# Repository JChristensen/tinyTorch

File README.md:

# tinyTorch #
https://github.com/JChristensen/tinyTorch  
https://github.com/JChristensen/tinyTorch-fw  
README file  
Jack Christensen Jan-2017

## Introduction ##

**tinyTorch** is a small LED flashlight controlled by an [ATtiny84A](http://www.atmel.com/devices/ATTINY84A.aspx) microcontroller. Choose white light for best illumination, or red light to preserve night vision. Eight brightness levels are selectable. The circuit can be programmed to power off automatically; two power-off intervals are available.

**tinyTorch** runs on two AA cells. Any type will work, including alkaline, standard carbon/zinc or rechargeable types (NiMH, NiCd). A boost regulator keeps the supply voltage and therefore the LED brightness constant as the batteries age. Because of the boost circuit, **tinyTorch** can run on batteries that will no longer power other devices, more nearly extracting all the energy available from the batteries. The microcontroller monitors the voltage and automatically shuts the circuit off when the batteries are exhausted to prevent leakage.

[Hardware design](https://github.com/JChristensen/tinyTorch) and [firmware](https://github.com/JChristensen/tinyTorch-fw) are available on GitHub.  
PC boards can be ordered from [OSH Park](https://www.oshpark.com/shared_projects/fUhQEilO).  
A bill of materials is available at [Mouser Electronics](https://www.mouser.com/ProjectManager/ProjectDetail.aspx?AccessID=e556f7b439) and also in the [hardware repo](https://github.com/JChristensen/tinyTorch).

## Operation ##

Press either button to turn **tinyTorch** on. The last color and brightness are remembered.
Press UP/COLOR to increase brightness; press DOWN/OFF to decrease.
Press and hold UP/COLOR to change between the white and red LEDs.
Press and hold DOWN/OFF to turn off.

To program **tinyTorch** to turn off automatically after one minute:
- Remove one battery.
- Press and hold the DOWN/OFF button.
- Insert the battery.
- Release DOWN/OFF.

To program **tinyTorch** to turn off automatically after five minutes, use the steps above but press and hold the UP/COLOR button instead.

To disable the automatic turn-off feature, use the steps above but press and hold both buttons instead.

When the batteries are exhausted, **tinyTorch** will blink the red and white LEDs alternately and then turn off. The brightness levels will be set to the minimum values. This may allow **tinyTorch** to continue to operate at a lower brightness level for a limited time but it is advisable to replace the batteries soon to prevent leakage.

## CC BY-SA ##
"tinyTorch" by Jack Christensen is licensed under [CC BY-SA 4.0](https://creativecommons.org/licenses/by-sa/4.0/).

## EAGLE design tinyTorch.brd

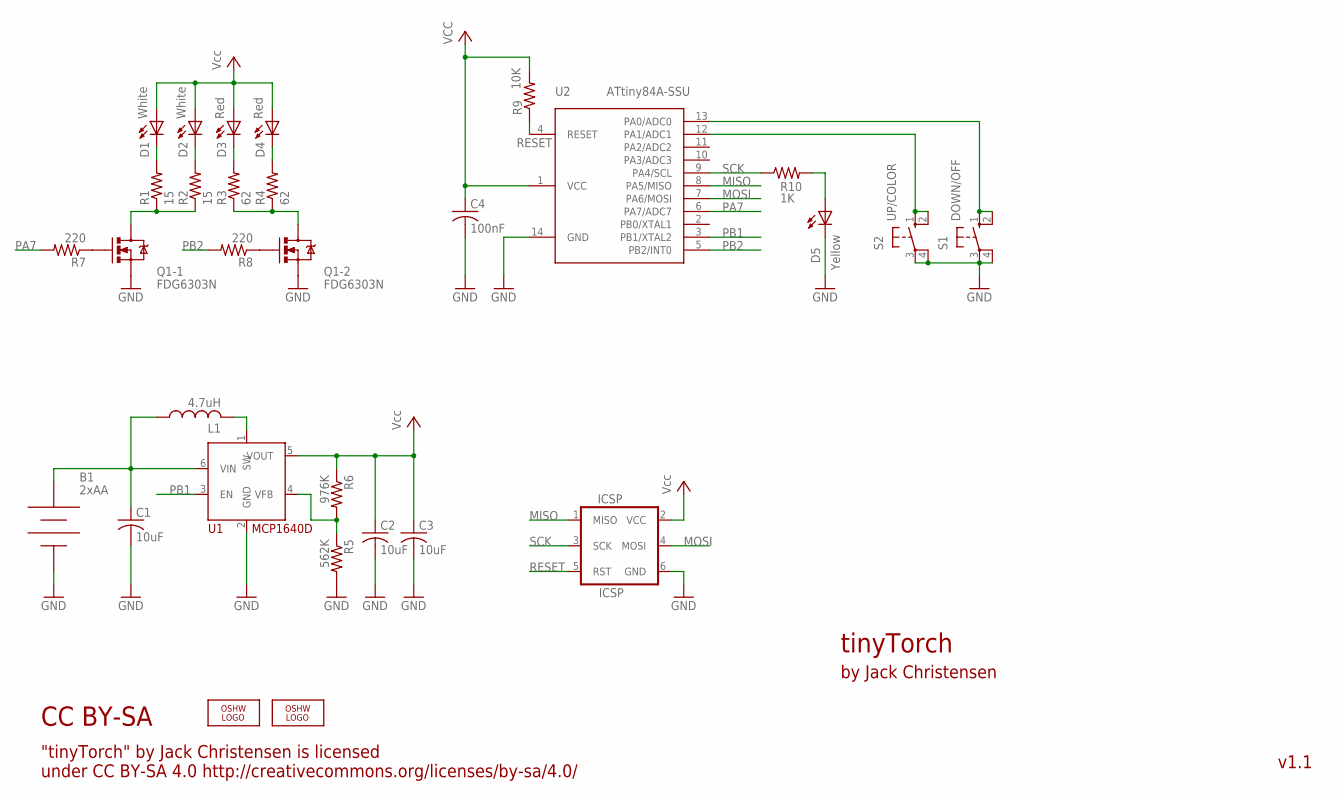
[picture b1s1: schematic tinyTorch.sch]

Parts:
B1: 2xAA; KEYSTONE-2462-NO-HOLES
C1, C2, C3: 10uF; M0805
C4: 100nF; M0805
D1, D2: White; LED5MM-OVAL
D3, D4: Red; LED5MM-OVAL
D5: Yellow; D0805A
ICSP: ICSP; 2X3_LOCK
L1: 4.7uH; C1210K
LOGO1: OSHW_LOGO_8MILX0150-NT; OSHW_8X150_NOTEXT
LOGO2: OSHW_LOGO_10MILX0200-NT; OSHW_10X200_NOTEXT
Q1: FDG6303N; SOT363_PHILIPS
R1, R2: 15; M0805
R3, R4: 62; M0805
R5: 562K; M0805
R6: 976K; M0805
R7, R8: 220; M0805
R9: 10K; M0805
R10: 1K; M0805
S1: DOWN/OFF; TACT-SW-SMT
S2: UP/COLOR; TACT-SW-SMT
U1: MCP1640D; SOT23-6
U2: ATtiny84A-SSU; SO14

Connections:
GND: B1.NEG, C1.2, C2.2, C3.2, C4.2, D5.K (C), ICSP.6 (GND), Q1.1 (S), Q1.4 (S), R5.2, S1.3, S1.4 (P1), S2.3, S2.4 (P1), U1.2 (GND), U2.14 (GND)
MISO: ICSP.1 (MISO), U2.8 (PA5/MISO)
MOSI: ICSP.4 (MOSI), U2.7 (PA6/MOSI)
unnamed: Q1.2 (G), R7.1
unnamed: R5.1, R6.2, U1.4 (VFB)
unnamed: Q1.5 (G), R8.1
unnamed: D1.K (C), R1.2
unnamed: D5.A, R10.2
unnamed: L1.2, U1.1 (SW)
unnamed: D4.K (C), R4.2
unnamed: D2.K (C), R2.2
unnamed: D3.K (C), R3.2
unnamed: B1.POS, C1.1, L1.1, U1.6 (VIN)
unnamed: Q1.6 (D), R1.1, R2.1
unnamed: Q1.3 (D), R3.1, R4.1
unnamed: S1.1 (S), S1.2 (S1), U2.13 (PA0/ADC0)
unnamed: S2.1 (S), S2.2 (S1), U2.12 (PA1/ADC1)
PA7: R7.2, U2.6 (PA7/ADC7)
PB1: U1.3 (EN), U2.3 (PB1/XTAL2)
PB2: R8.2, U2.5 (PB2/INT0)
RESET: ICSP.5 (RST), R9.1, U2.4 (RESET)
SCK: ICSP.3 (SCK), R10.1, U2.9 (PA4/SCL)
VCC: C2.1, C3.1, C4.1, D1.A, D2.A, D3.A, D4.A, ICSP.2 (VCC), R6.1, R9.2, U1.5 (VOUT), U2.1 (VCC)

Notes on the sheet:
"tinyTorch" by Jack Christensen is licensed under CC BY-SA 4.0 http://creativecommons.org/licenses/by-sa/4.0/
CC BY-SA
tinyTorch
by Jack Christensen
v1.1

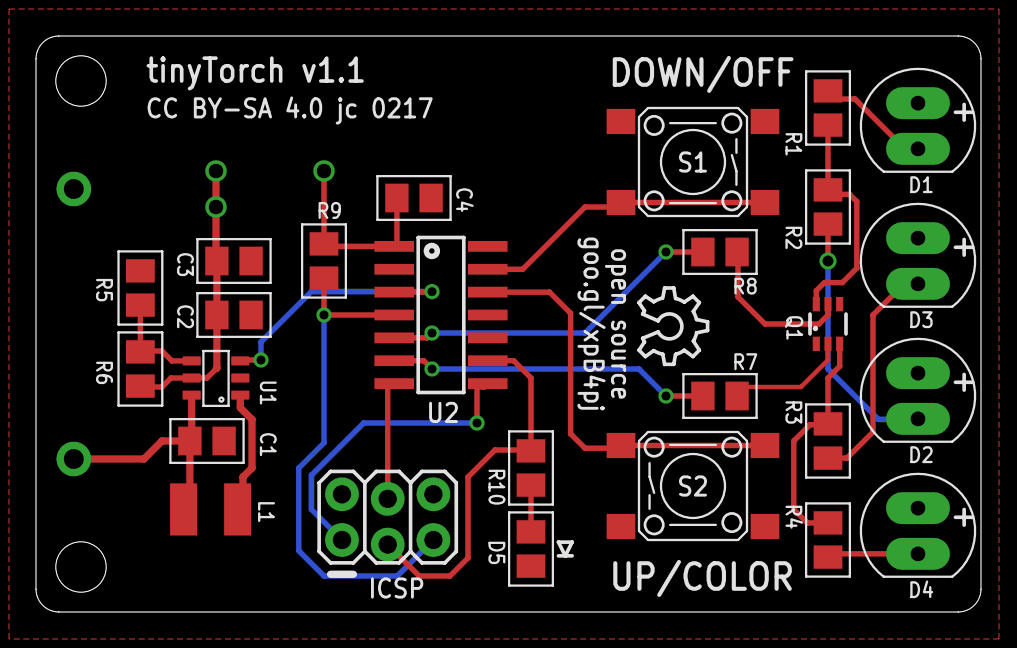
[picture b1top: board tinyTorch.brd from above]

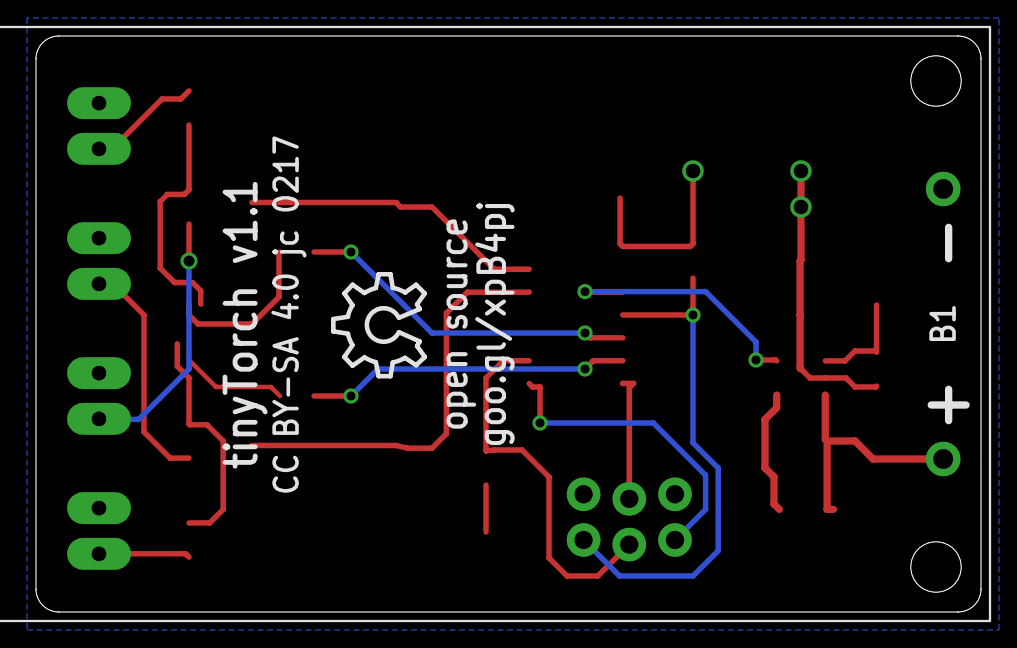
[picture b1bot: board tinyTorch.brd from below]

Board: 2 copper layers, 52.5 x 32.0 mm, 29 parts (2 on the bottom side), 23 nets.

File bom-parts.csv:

"Part";"Value";"Device";"Package";"Description";"MFR";"MFR-PART-NO";
"B1";"2xAA";"BATTERY-2AANOHOLES";"KEYSTONE-2462-NO-HOLES";"";"Keystone";"2462";
"C1";"10uF";"C-USM0805";"M0805";"CAPACITOR, American symbol";"";"";
"C2";"10uF";"C-USM0805";"M0805";"CAPACITOR, American symbol";"";"";
"C3";"10uF";"C-USM0805";"M0805";"CAPACITOR, American symbol";"";"";
"C4";"100nF";"C-USM0805";"M0805";"CAPACITOR, American symbol";"";"";
"D1";"White";"LED5MM-LONGPADS";"LED5MM-OVAL";"LED";"Cree";"C503D-WAN-CCBEB151";
"D2";"White";"LED5MM-LONGPADS";"LED5MM-OVAL";"LED";"Cree";"C503D-WAN-CCBEB151";
"D3";"Red";"LED5MM-LONGPADS";"LED5MM-OVAL";"LED";"Lite-On";"LTL2H3EZ1K";
"D4";"Red";"LED5MM-LONGPADS";"LED5MM-OVAL";"LED";"Lite-On";"LTL2H3EZ1K";
"D5";"Yellow";"LEDD0805A";"D0805A";"LED";"Lite-On";"LTST-C171KYKT";
"ICSP";"ICSP";"AVR_SPI_PRG_62X3_LOCK";"2X3_LOCK";"AVR ISP 6 Pin";"";"";
"L1";"4.7uH";"INDUCTORC1210K";"C1210K";"Murata #11R472C";"Taiyo Yuden";"CBC3225T4R7MR";
"LOGO1";"OSHW_LOGO_8MILX0150-NT";"OSHW_LOGO_8MILX0150-NT";"OSHW_8X150_NOTEXT";"";"";"";
"LOGO2";"OSHW_LOGO_10MILX0200-NT";"OSHW_LOGO_10MILX0200-NT";"OSHW_10X200_NOTEXT";"";"";"";
"Q1";"FDG6303N";"DUAL-MOSFET";"SOT363_PHILIPS";"e.g. Fairchild/ON Semi FDG6303N";"";"";
"R1";"15";"R-US_M0805";"M0805";"RESISTOR, American symbol";"";"";
"R2";"15";"R-US_M0805";"M0805";"RESISTOR, American symbol";"";"";
"R3";"62";"R-US_M0805";"M0805";"RESISTOR, American symbol";"";"";
"R4";"62";"R-US_M0805";"M0805";"RESISTOR, American symbol";"";"";
"R5";"562K";"R-US_M0805";"M0805";"RESISTOR, American symbol";"";"";
"R6";"976K";"R-US_M0805";"M0805";"RESISTOR, American symbol";"";"";
"R7";"220";"R-US_M0805";"M0805";"RESISTOR, American symbol";"";"";
"R8";"220";"R-US_M0805";"M0805";"RESISTOR, American symbol";"";"";
"R9";"10K";"R-US_M0805";"M0805";"RESISTOR, American symbol";"";"";
"R10";"1K";"R-US_M0805";"M0805";"RESISTOR, American symbol";"";"";
"S1";"DOWN/OFF";"10-XXSMT";"TACT-SW-SMT";"OMRON SWITCH";"Omron";"B3FS-1000";
"S2";"UP/COLOR";"10-XXSMT";"TACT-SW-SMT";"OMRON SWITCH";"Omron";"B3FS-1000";
"U1";"MCP1640D";"MCP1640";"SOT23-6";"";"";"";
"U2";"ATtiny84A-SSU";"ATTINYX4SO14";"SO14";"";"";"";

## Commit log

2017-01-30 Initial commit.
2017-01-31 v1 as sent to fab.
2017-01-31 Tweak resistor values.
2017-01-31 Update doc, bom, small board image.
2017-01-31 Update README.
2017-02-04 Update README, board and schematic images.
2017-02-14 Add board photo.
2017-03-30 Minor board layout tweaks.

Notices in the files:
tinyTorch.brd:
CC BY-SA 4.0 jc 0217
